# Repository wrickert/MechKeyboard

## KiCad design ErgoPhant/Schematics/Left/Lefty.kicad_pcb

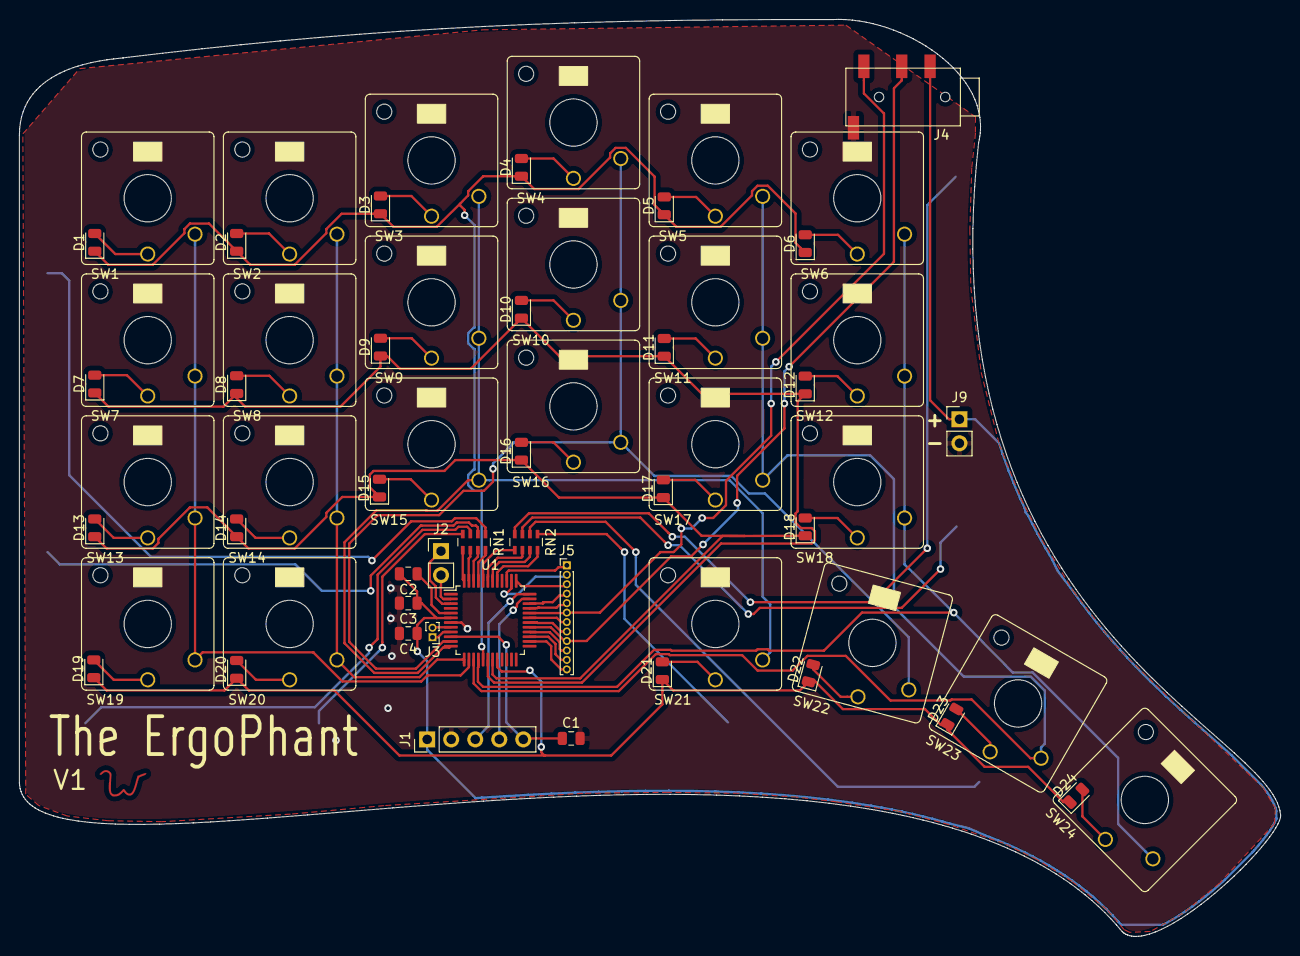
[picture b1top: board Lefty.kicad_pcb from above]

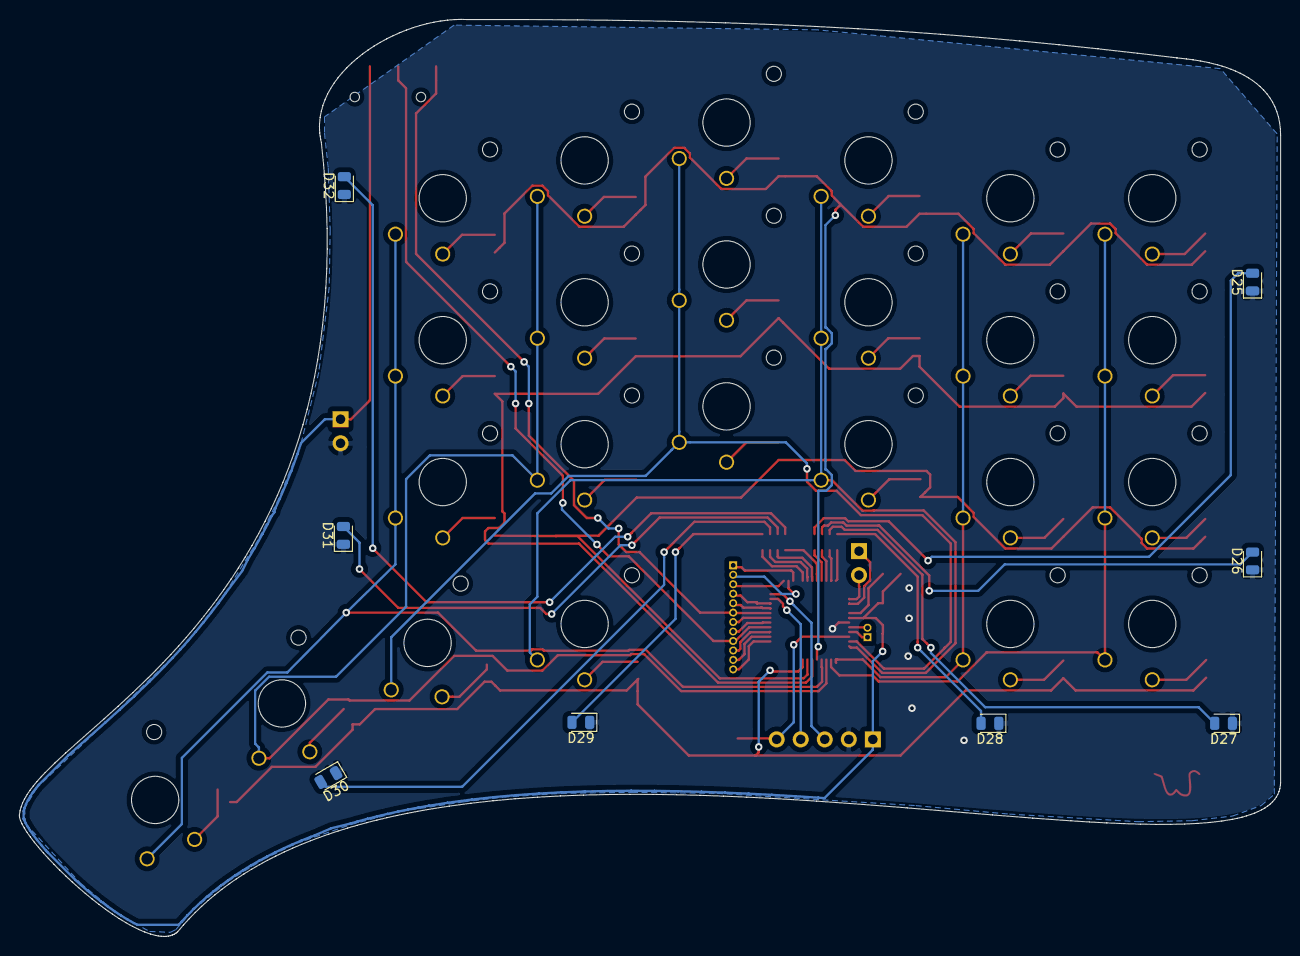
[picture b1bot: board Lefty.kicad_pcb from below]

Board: 2 copper layers, 133.3 x 96.9 mm, 70 parts (8 on the bottom side), 72 nets.

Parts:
C1, C2, C4: 100nF; C_0805_2012Metric
C3: 4.7uF; C_0805_2012Metric
D1, D2, D3, D4, D5, D6, D7, D8, D9, D10, D11, D12, D13, D14, D15, D16, D17, D18, D19, D20, D21, D22, D23, D24: D; D_0805_2012Metric
D25, D26, D27, D28, D29, D30, D31, D32: LED_Small; LED_0805_2012Metric
J1: Prog; PinHeader_1x05_P2.54mm_Vertical
J2: Conn_01x02; PinHeader_1x02_P2.54mm_Vertical
J3: Conn_01x02; PinHeader_1x02_P1.00mm_Vertical
J4: LeftConn; PJ-320D-4A_TRRS3.5
J5: GPIO; PinHeader_1x12_P1.00mm_Vertical
J9: PwrLeft; PinHeader_1x02_P2.54mm_Vertical
RN1, RN2: 330; R_Array_Concave_4x0603
Ref**: Val**; W
SW1, SW2, SW3, SW4, SW5, SW6, SW7, SW8, SW9, SW10, SW11, SW12, SW13, SW14, SW15, SW16, SW17, SW18, SW19, SW20, SW21, SW22, SW23, SW24: Switch; KailhChocolateV2
U1: STM32G030C8T6; LQFP-48_7x7mm_P0.5mm

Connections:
C1: SW1.2, SW7.2, SW13.2, SW19.2, U1.14
C2: SW2.2, SW8.2, SW14.2, SW20.2, U1.13
C3: SW3.2, SW9.2, SW15.2, SW21.2, U1.12
C4: SW4.2, SW10.2, SW16.2, SW22.2, U1.11
C5: SW5.2, SW11.2, SW17.2, SW23.2, U1.15
C6: SW6.2, SW12.2, SW18.2, SW24.2, U1.16
GPIO1: J5.1, U1.39
GPIO2: J5.2, U1.38
GPIO3: J5.3, U1.37
GPIO4: J5.4, U1.34
GPIO5: J5.5, U1.33
GPIO6: J5.7, U1.31
GPIO7: J5.8, U1.30
GPIO8: J5.10, U1.28
GPIO9: J5.11, U1.27
GPIO10: J5.12, U1.26
L1: D1.1, D2.1, D3.1, D4.1, D5.1, D6.1, U1.17
L2: D7.1, D8.1, D9.1, D10.1, D11.1, D12.1, U1.18
L3: D13.1, D14.1, D15.1, D16.1, D17.1, D18.1, U1.19
L4: D19.1, D20.1, D21.1, D22.1, D23.1, D24.1, U1.20
LLed1: RN1.5, U1.48
LLed2: RN1.6, U1.47
LLed3: RN1.7, U1.46
LLed4: RN1.8, U1.45
LLed5: RN2.5, U1.44
LLed6: RN2.6, U1.43
LLed7: RN2.7, U1.42
LLed8: RN2.8, U1.41
unnamed: C2.1, U1.5
unnamed: D1.2, SW1.1
unnamed: D2.2, SW2.1
unnamed: D3.2, SW3.1
unnamed: D4.2, SW4.1
unnamed: D5.2, SW5.1
unnamed: D6.2, SW6.1
unnamed: D7.2, SW7.1
unnamed: D8.2, SW8.1
unnamed: D9.2, SW9.1
unnamed: D10.2, SW10.1
unnamed: D11.2, SW11.1
unnamed: D12.2, SW12.1
unnamed: D13.2, SW13.1
unnamed: D14.2, SW14.1
unnamed: D15.2, SW15.1
unnamed: D16.2, SW16.1
unnamed: D17.2, SW17.1
unnamed: D18.2, SW18.1
unnamed: D19.2, SW19.1
unnamed: D20.2, SW20.1
unnamed: D21.2, SW21.1
unnamed: D22.2, SW22.1
unnamed: D23.2, SW23.1
unnamed: D24.2, SW24.1
unnamed: D25.2, RN1.1
unnamed: D26.2, RN1.2
unnamed: D27.2, RN1.3
unnamed: D28.2, RN1.4
unnamed: D29.2, RN2.1
unnamed: D30.2, RN2.2
unnamed: D31.2, RN2.3
unnamed: D32.2, RN2.4
unnamed: J2.1, U1.3
unnamed: J2.2, U1.2
unnamed: J3.1, U1.9
unnamed: J3.2, U1.8
RST: C1.1, J1.5, U1.10
SCL: J4.3, J5.9, U1.29
SDA: J4.2, J5.6, U1.32
SWCLK: J1.3, U1.36
SWDIO: J1.4, U1.35
VCC: C2.2, C3.1, C4.1, J1.1, J4.4, J9.1, U1.6
VSS: C1.2, C3.2, C4.2, D25.1, D26.1, D27.1, D28.1, D29.1, D30.1, D31.1, D32.1, J1.2, J4.1, J9.2, U1.7
